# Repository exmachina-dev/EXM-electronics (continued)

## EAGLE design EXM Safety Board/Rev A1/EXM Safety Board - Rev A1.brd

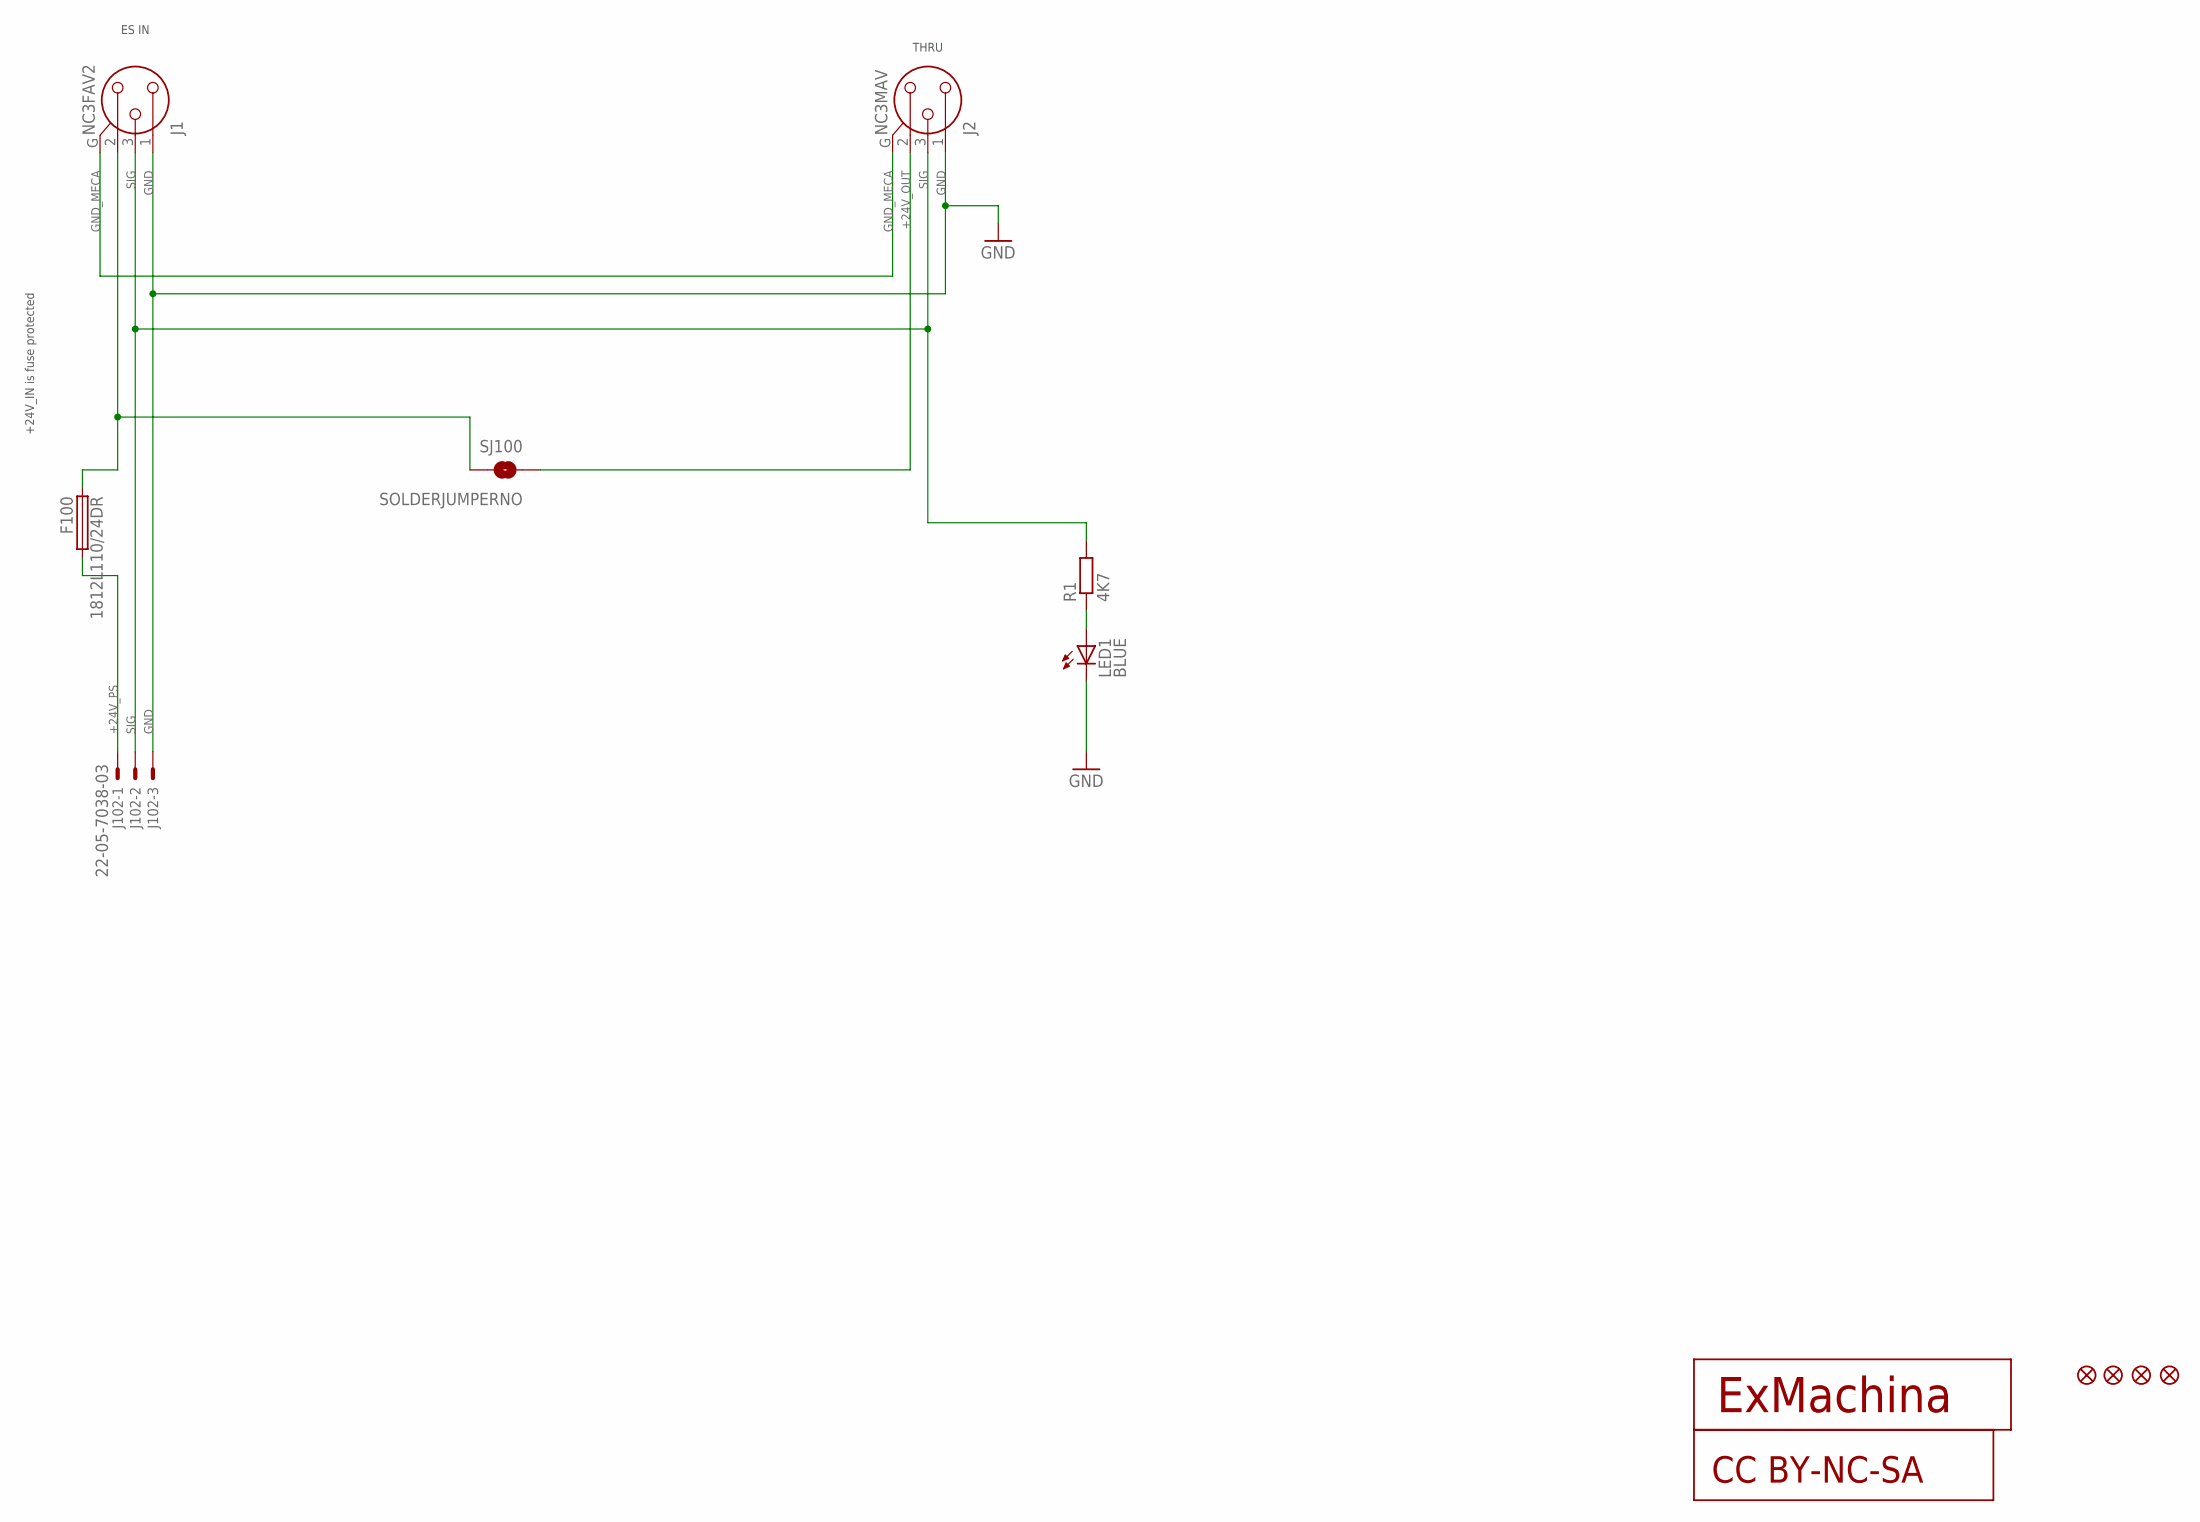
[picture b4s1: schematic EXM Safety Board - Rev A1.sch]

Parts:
CC100: CC-BY-NC-SA
F100: 1812L110/24DR; LITTLEFUSE_SMD; MPN 1812L110/24DR
J1: NC3FAV2
J2: NC3MAV
J102: 22-05-7038-03; 7395-03
JP100, JP101, JP102, JP103: FIDUCIAL1X2; FIDUCIAL-1X2
LED1: BLUE; CHIPLED_0603; MPN OVS-0603
R1: 4K7; R0603; MPN RC0603FR-074K7L
SJ100: SOLDERJUMPERNO; SJ_2S-NO
T100: EXMACHINA-LOGO-NAME; EXM-LOGO-BASELINE

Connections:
+24V_IN: F100.1, J1.2, SJ100.2
+24V_OUT: J2.2, SJ100.1
+24V_PS: F100.2, J102.1
GND: J1.1, J2.1, J102.3, LED1.C
GND_MECA: J1.G, J2.G
unnamed: LED1.A, R1.1
SIG: J1.3, J2.3, J102.2, R1.2

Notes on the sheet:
+24V_IN is fuse protected
ES IN
THRU

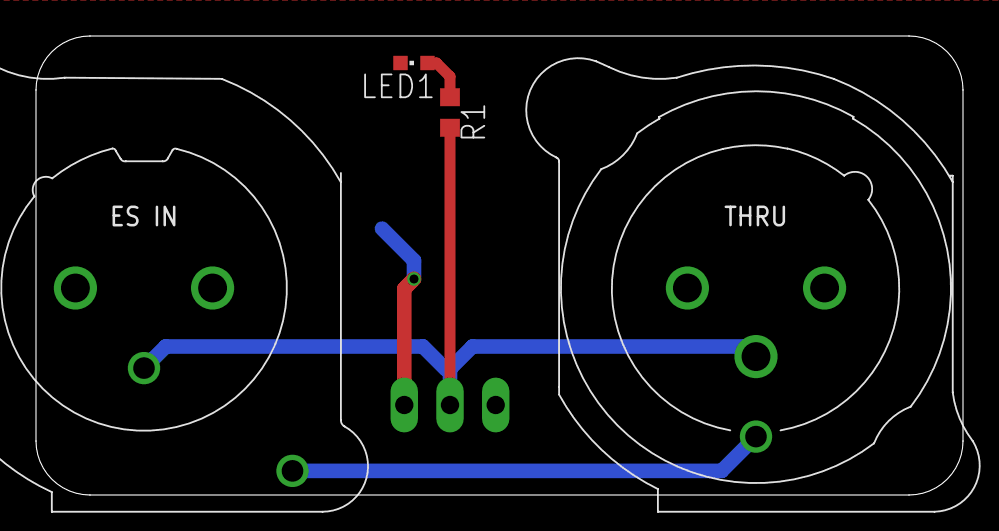
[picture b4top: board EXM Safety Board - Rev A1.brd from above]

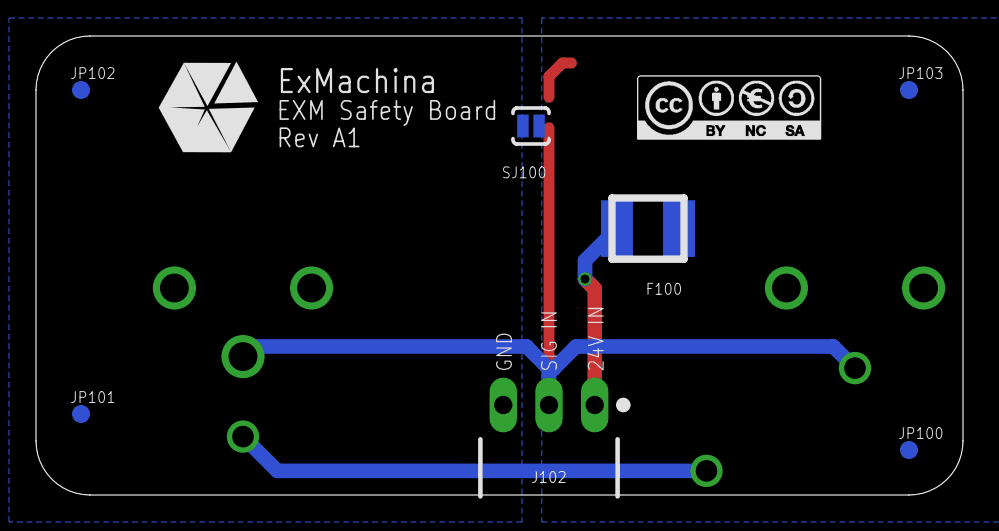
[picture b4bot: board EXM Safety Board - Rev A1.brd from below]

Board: 2 copper layers, 51.5 x 25.5 mm, 14 parts (9 on the bottom side), 7 nets.

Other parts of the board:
U$1: A4L-LOC

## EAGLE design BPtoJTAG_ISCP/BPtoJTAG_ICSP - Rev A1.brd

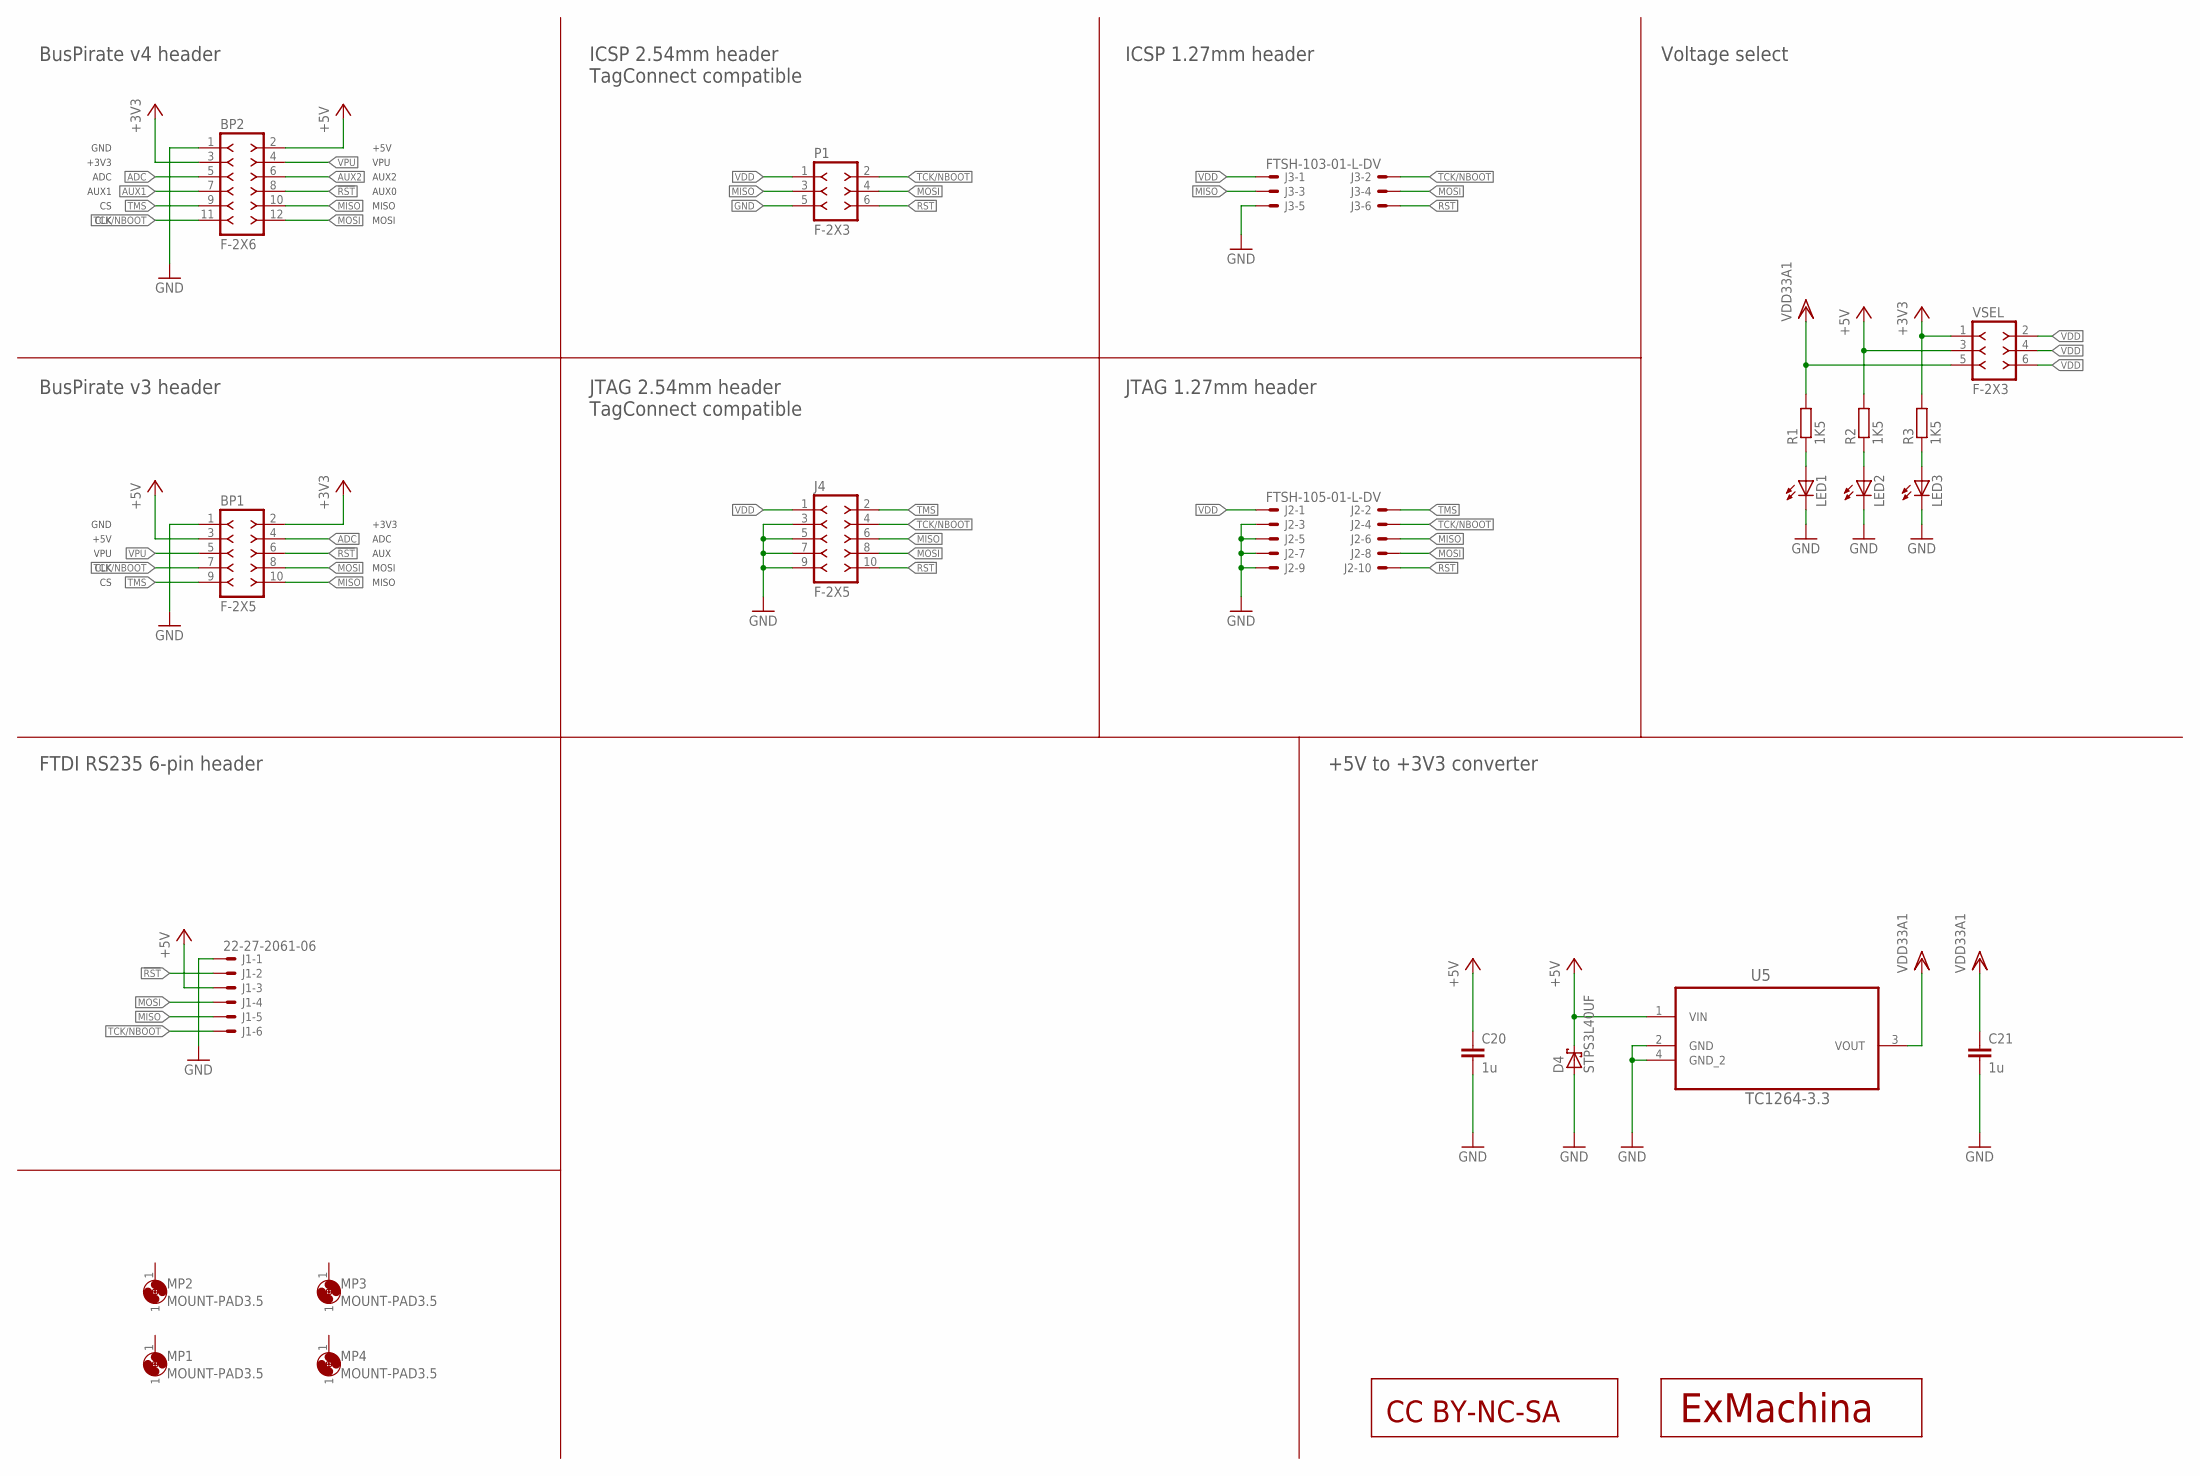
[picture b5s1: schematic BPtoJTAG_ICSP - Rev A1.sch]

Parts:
BP1: F-2X5; DIL-100-2X5
BP2: F-2X6; DIL-100-2X6
C20, C21: 1u; C0603
CC1: CC-BY-NC-SA
D4: STPS3L40UF; SMB
J1: 22-27-2061-06; 6410-06
J2: FTSH-105-01-L-DV
J3: FTSH-103-01-L-DV
J4: F-2X5; DIL-100-2X5
LED1, LED2, LED3: LEDCHIPLED_0603; CHIPLED_0603
MP1, MP2, MP3, MP4: MOUNT-PAD3.5; P3,5
P1: F-2X3; DIL-100-2X3
R1, R2, R3: 1K5; R0603
T1: EXMACHINA-LOGO-NAME; EXM-LOGO-BASELINE
U5: TC1264-3.3; SOT230P700X180-4N
VSEL: F-2X3; DIL-100-2X3

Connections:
!RST: BP1.6, BP2.8, J1.2, J2.10, J3.6, J4.10, P1.6
+3V3: BP1.2, BP2.3, R3.2, VSEL.1
+5V: BP1.3, BP2.2, C20.1, D4.C, J1.3, R2.2, U5.1 (VIN), VSEL.3
ADC: BP1.4, BP2.5
AUX1: BP2.7
AUX2: BP2.6
GND: BP1.1, BP2.1, C20.2, C21.2, D4.A, J1.1, J2.3, J2.5, J2.7, J2.9, J3.5, J4.3, J4.5, J4.7, J4.9, LED1.C, LED2.C, LED3.C, P1.5, U5.2 (GND), U5.4 (GND_2)
MISO: BP1.10, BP2.10, J1.5, J2.6, J3.3, J4.6, P1.3
MOSI: BP1.8, BP2.12, J1.4, J2.8, J3.4, J4.8, P1.4
unnamed: LED1.A, R1.1
unnamed: LED2.A, R2.1
unnamed: LED3.A, R3.1
TCK/NBOOT: BP1.7, BP2.11, J1.6, J2.4, J3.2, J4.4, P1.2
TMS: BP1.9, BP2.9, J2.2, J4.2
VDD: J2.1, J3.1, J4.1, P1.1, VSEL.2, VSEL.4, VSEL.6
VDD33A1: C21.1, R1.2, U5.3 (VOUT), VSEL.5
VPU: BP1.5, BP2.4

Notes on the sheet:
GND
+5V
VPU
CLK
+3V3
ADC
AUX
MOSI
MISO
AUX0
AUX2
AUX1
BusPirate v4 header
BusPirate v3 header
Voltage select
FTDI RS235 6-pin header
JTAG 1.27mm header
JTAG 2.54mm header TagConnect compatible
ICSP 2.54mm header TagConnect compatible
ICSP 1.27mm header
+5V to +3V3 converter

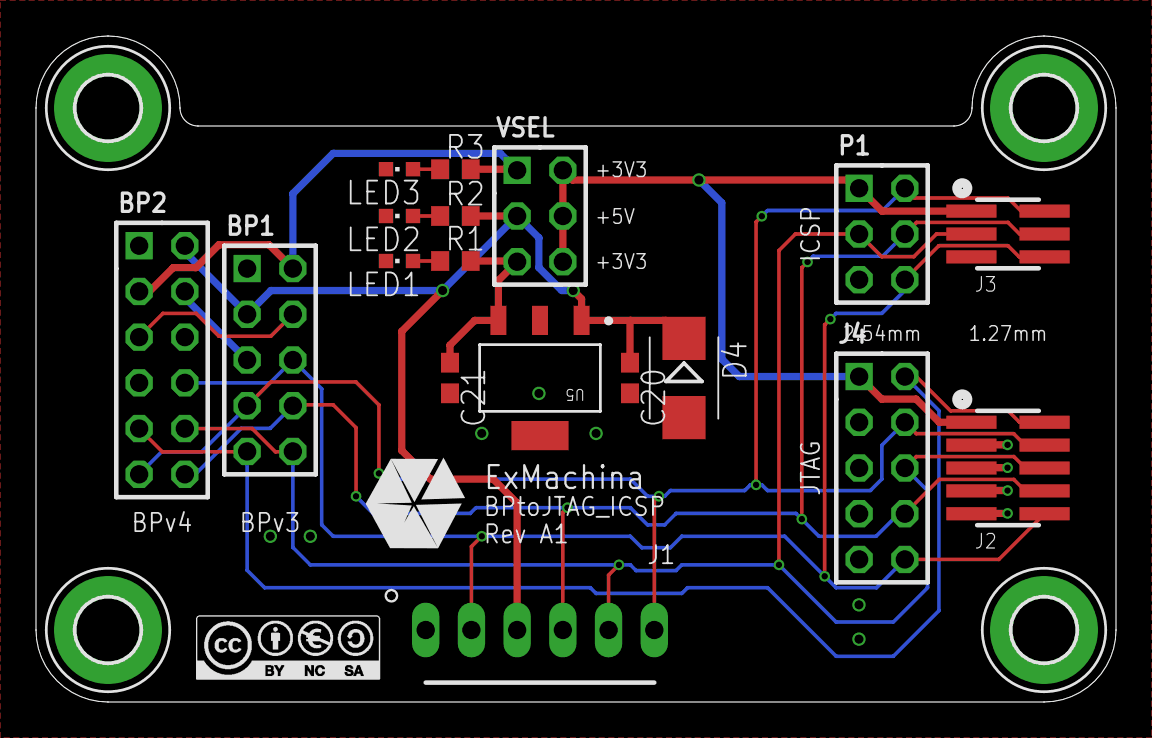
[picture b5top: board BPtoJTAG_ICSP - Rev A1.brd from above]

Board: 2 copper layers, 60.0 x 37.0 mm, 24 parts (0 on the bottom side), 15 nets.

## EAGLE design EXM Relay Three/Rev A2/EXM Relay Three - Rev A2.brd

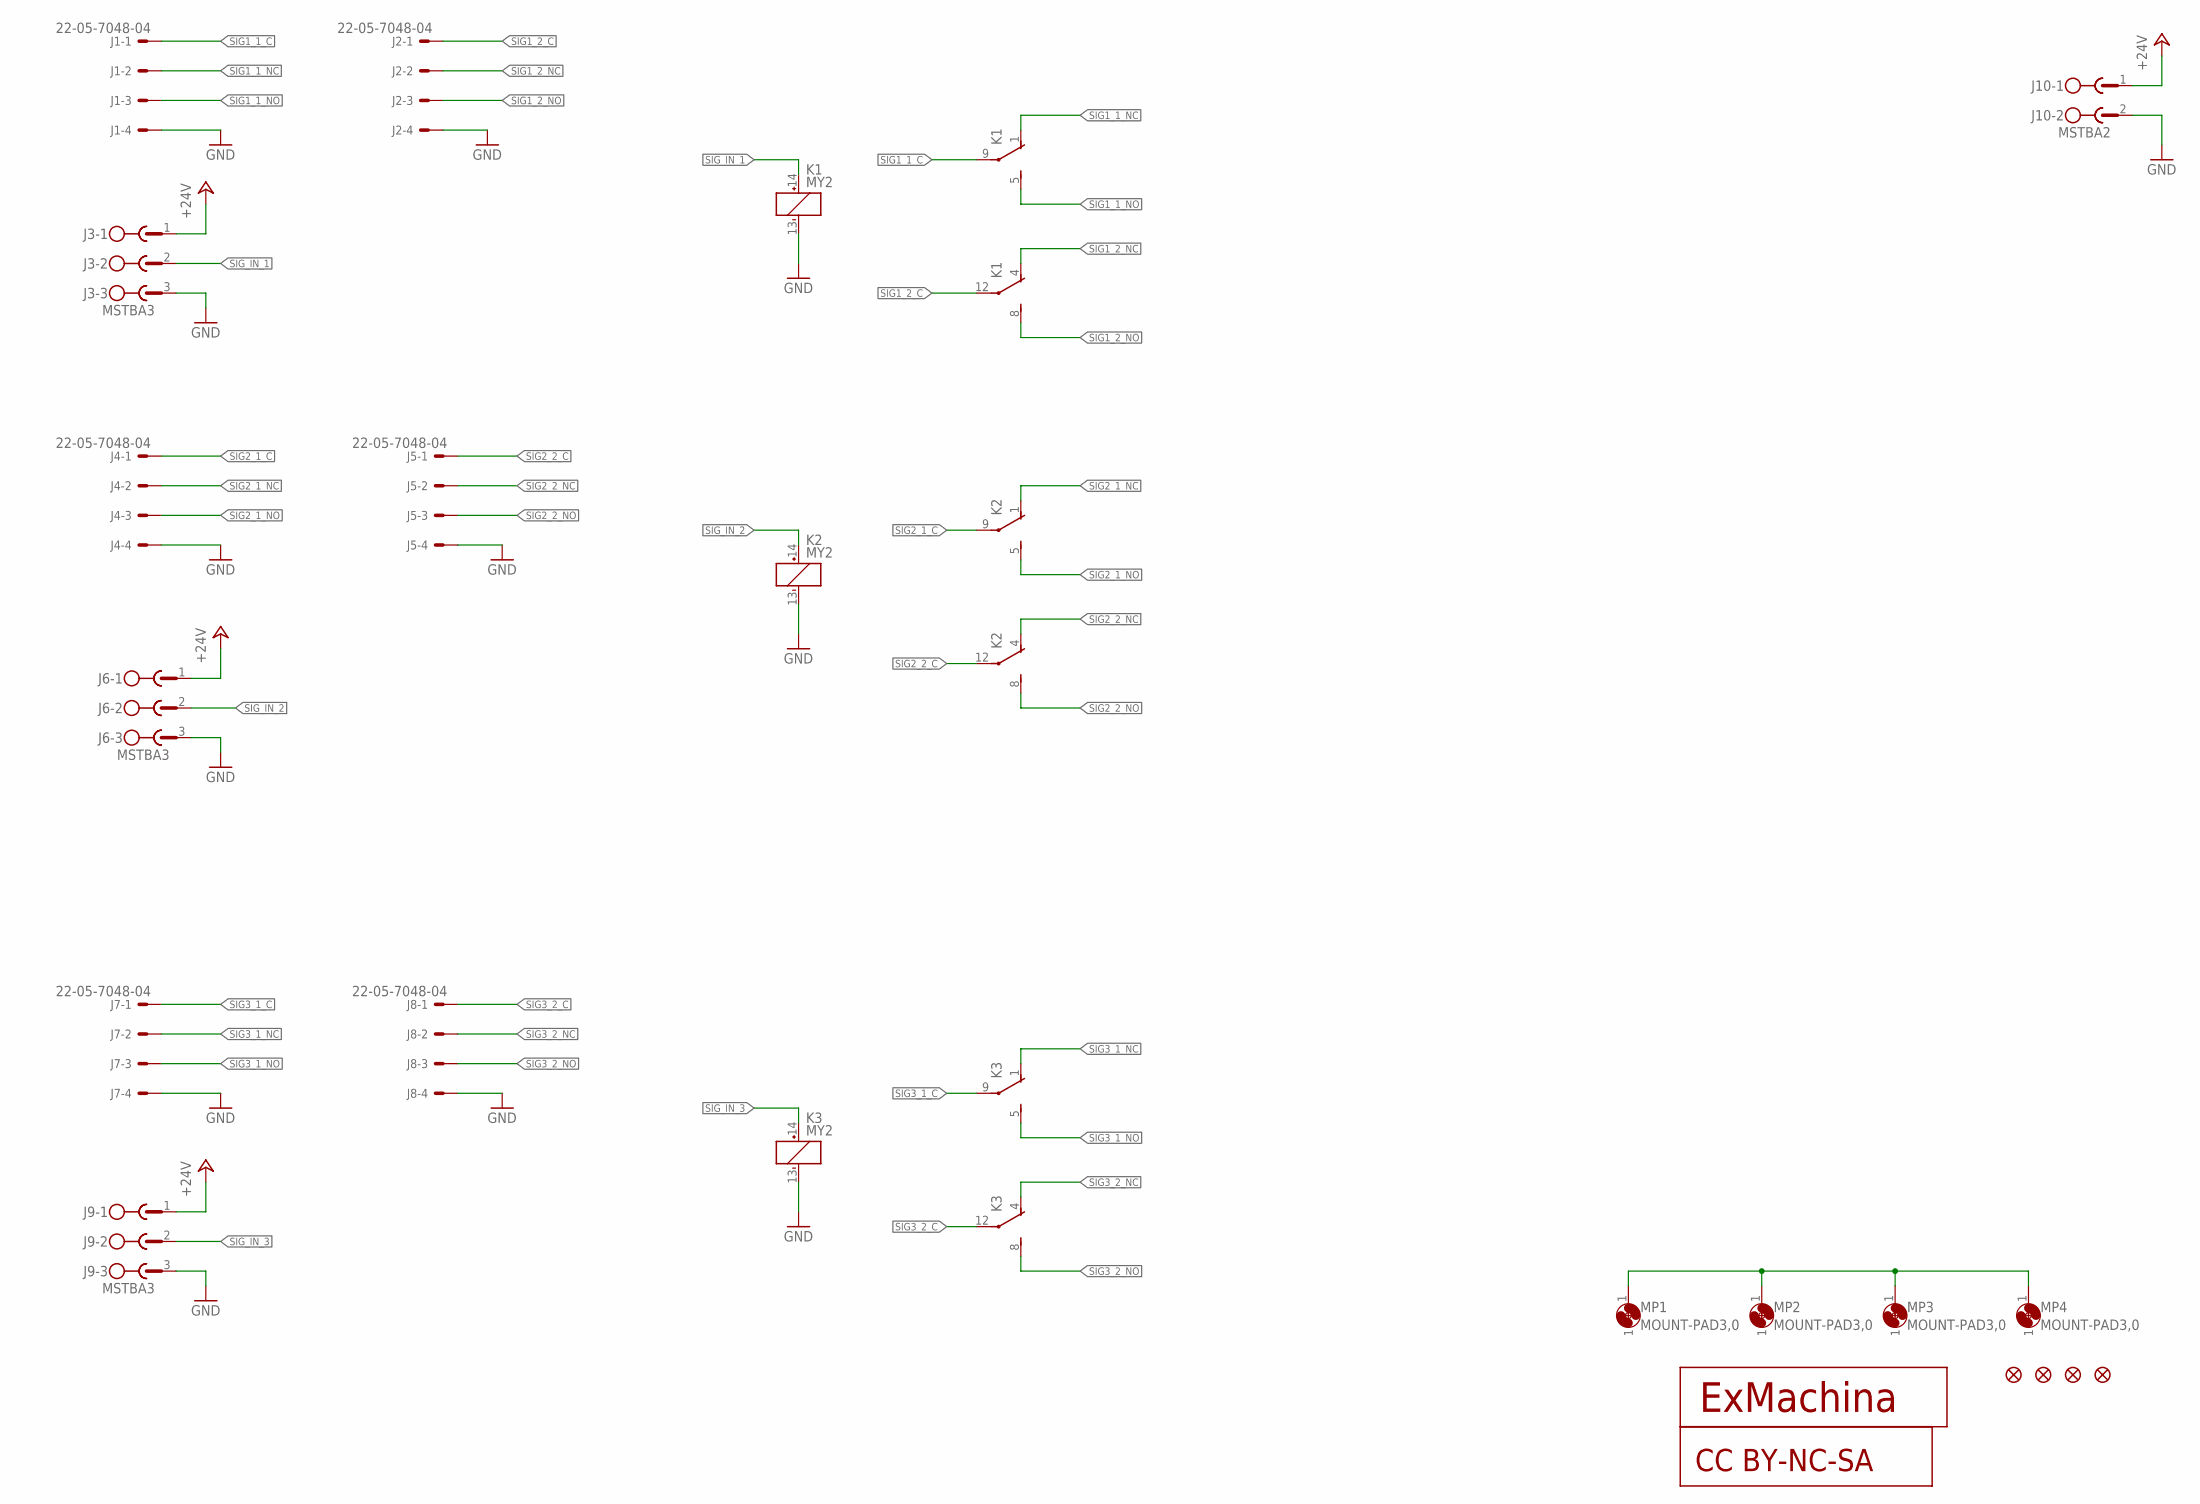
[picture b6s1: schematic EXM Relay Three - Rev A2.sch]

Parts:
CC1: CC-BY-NC-SA
J1, J2, J4, J5, J7, J8: 22-05-7048-04; 7395-04
J3, J6, J9: MSTBA3
J10: MSTBA2
JP1, JP2, JP3, JP4: FIDUCIAL1X2; FIDUCIAL-1X2
K1, K2, K3: MY2; PY08; MPN PY08
MP1, MP2, MP3, MP4: MOUNT-PAD3,0; P3,0
T1: EXMACHINA-LOGO-NAME; EXM-LOGO-BASELINE

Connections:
1: MP1.1, MP2.1, MP3.1, MP4.1
+24V: J3.1, J6.1, J9.1, J10.1
GND: J1.4, J2.4, J3.3, J4.4, J5.4, J6.3, J7.4, J8.4, J9.3, J10.2, K1.13 (-), K2.13 (-), K3.13 (-)
SIG1_1_C: J1.1, K1.9 (C)
SIG1_1_NC: J1.2, K1.1 (NC)
SIG1_1_NO: J1.3, K1.5 (NO)
SIG1_2_C: J2.1, K1.12 (C)
SIG1_2_NC: J2.2, K1.4 (NC)
SIG1_2_NO: J2.3, K1.8 (NO)
SIG2_1_C: J4.1, K2.9 (C)
SIG2_1_NC: J4.2, K2.1 (NC)
SIG2_1_NO: J4.3, K2.5 (NO)
SIG2_2_C: J5.1, K2.12 (C)
SIG2_2_NC: J5.2, K2.4 (NC)
SIG2_2_NO: J5.3, K2.8 (NO)
SIG3_1_C: J7.1, K3.9 (C)
SIG3_1_NC: J7.2, K3.1 (NC)
SIG3_1_NO: J7.3, K3.5 (NO)
SIG3_2_C: J8.1, K3.12 (C)
SIG3_2_NC: J8.2, K3.4 (NC)
SIG3_2_NO: J8.3, K3.8 (NO)
SIG_IN_1: J3.2, K1.14 (+)
SIG_IN_2: J6.2, K2.14 (+)
SIG_IN_3: J9.2, K3.14 (+)

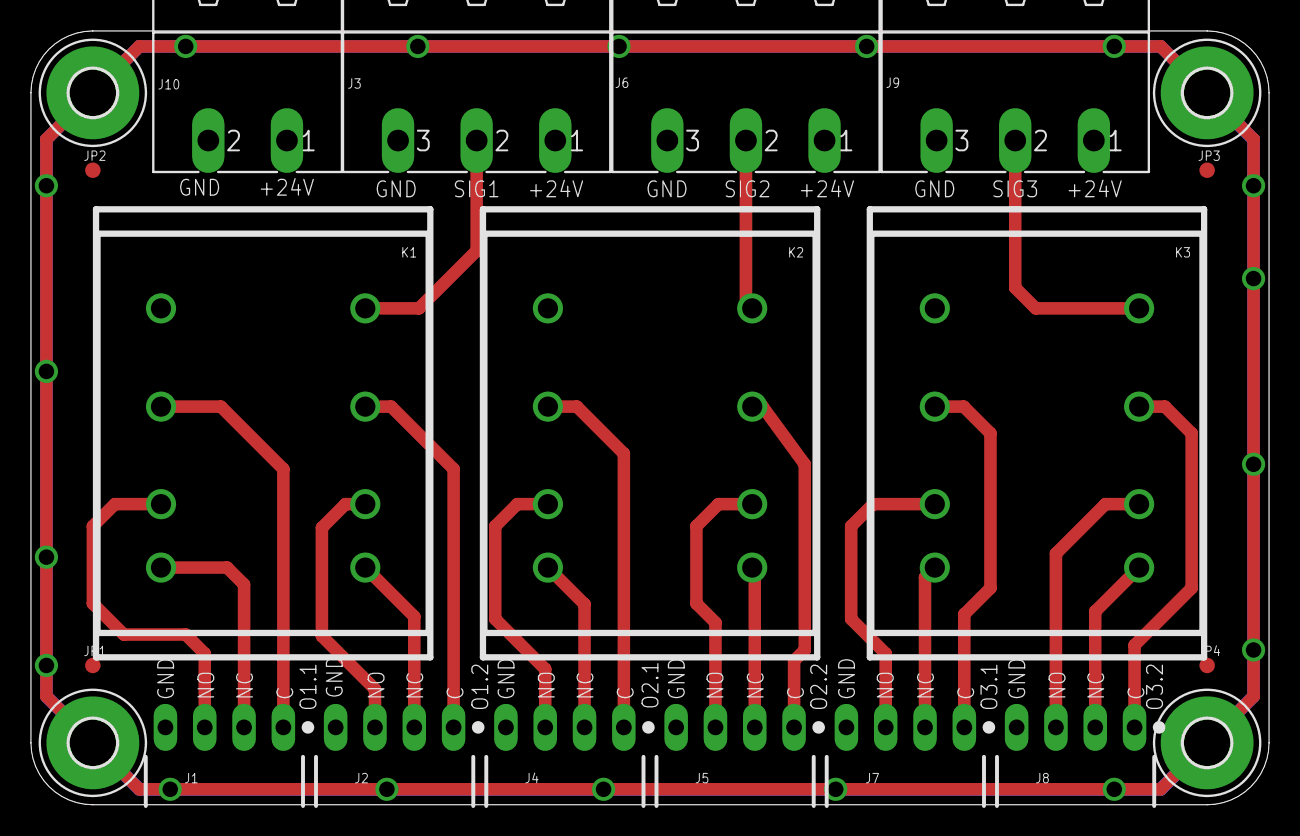
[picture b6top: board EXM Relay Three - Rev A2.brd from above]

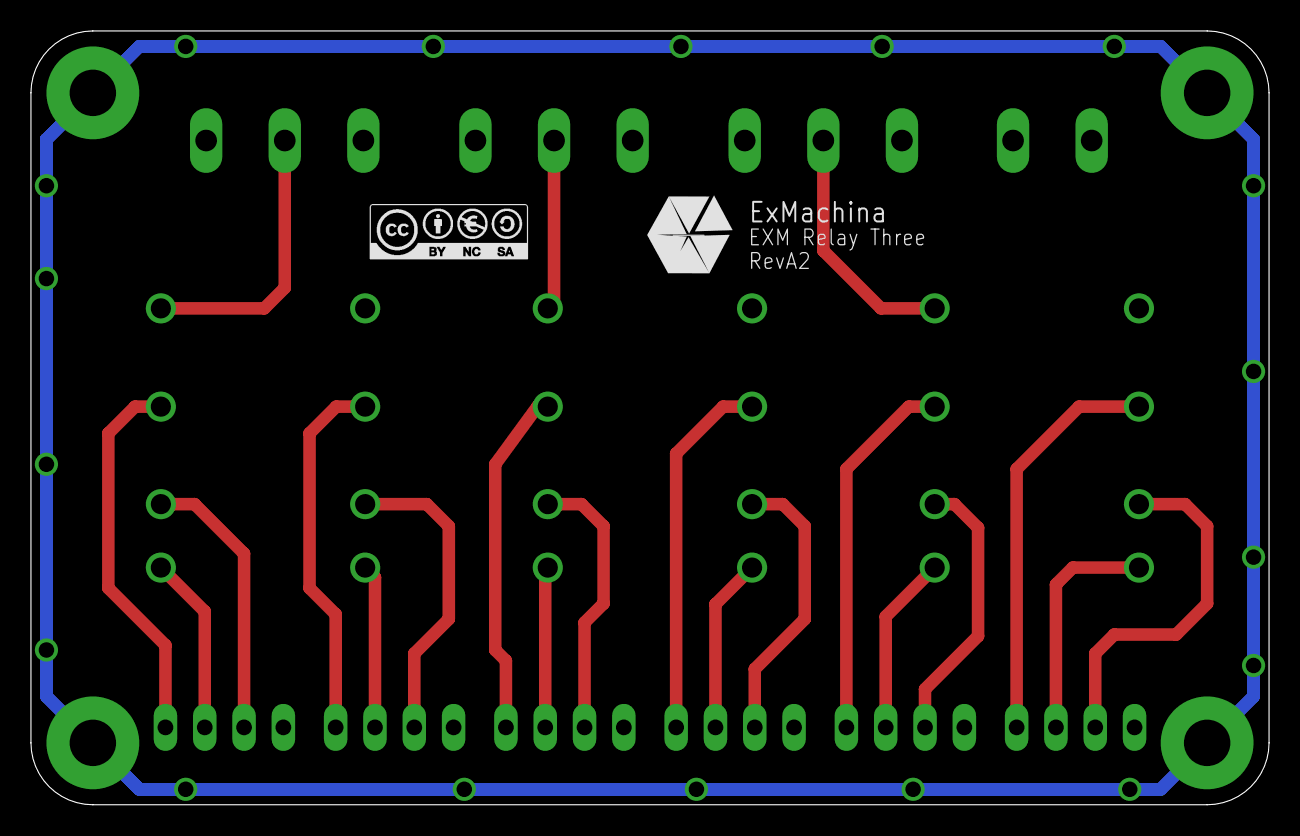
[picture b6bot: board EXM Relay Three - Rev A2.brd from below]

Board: 2 copper layers, 80.0 x 50.0 mm, 24 parts (2 on the bottom side), 24 nets.

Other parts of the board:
U$1: A4L-LOC

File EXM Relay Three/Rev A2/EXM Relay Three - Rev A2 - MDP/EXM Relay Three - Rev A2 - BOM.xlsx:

Qty | Designator | Value | Description | Package | Manufacteur | Reference Manufacteur | Mounting Tecghnologie | Mount
6 | J1, J2, J4, J5, J7, J8 | 22-05-7048 | Connecteur fil-à-carte, Angle Droit, 2.54 mm, 4 Contact(s), Embase, Série KK |  | MOLEX | 22-05-7048 | Thought-Hole | Yes
1 | J10 | MSTBA2 | Bornier, Embase, 5.08 mm, 2 Voies, 12 A, 250 V, Traversant angle droit |  | PHOENIX | 1757242 | Thought-Hole | Yes
3 | J3, J6, J9 | MSTBA3 | Bornier, Embase, 5.08 mm, 3 Voies, 12 A, 250 V, Traversant angle droit |  | PHOENIX | 1757255 | Thought-Hole | Yes
3 | K1, K2, K3 | PY08-02 | Embase relais, Traversant, Connexion rapide, 8 Broche(s), 7 A, 250 VAC, SUPER M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 |  | OMRON COMPONENTS USA | PY08-02 | Thought-Hole | Yes
3 |  | PYC-P2 | Accessoire pour relais, MY/LY Series, Maintien bas |  | OMRON COMPONENTS USA | PYC-P2

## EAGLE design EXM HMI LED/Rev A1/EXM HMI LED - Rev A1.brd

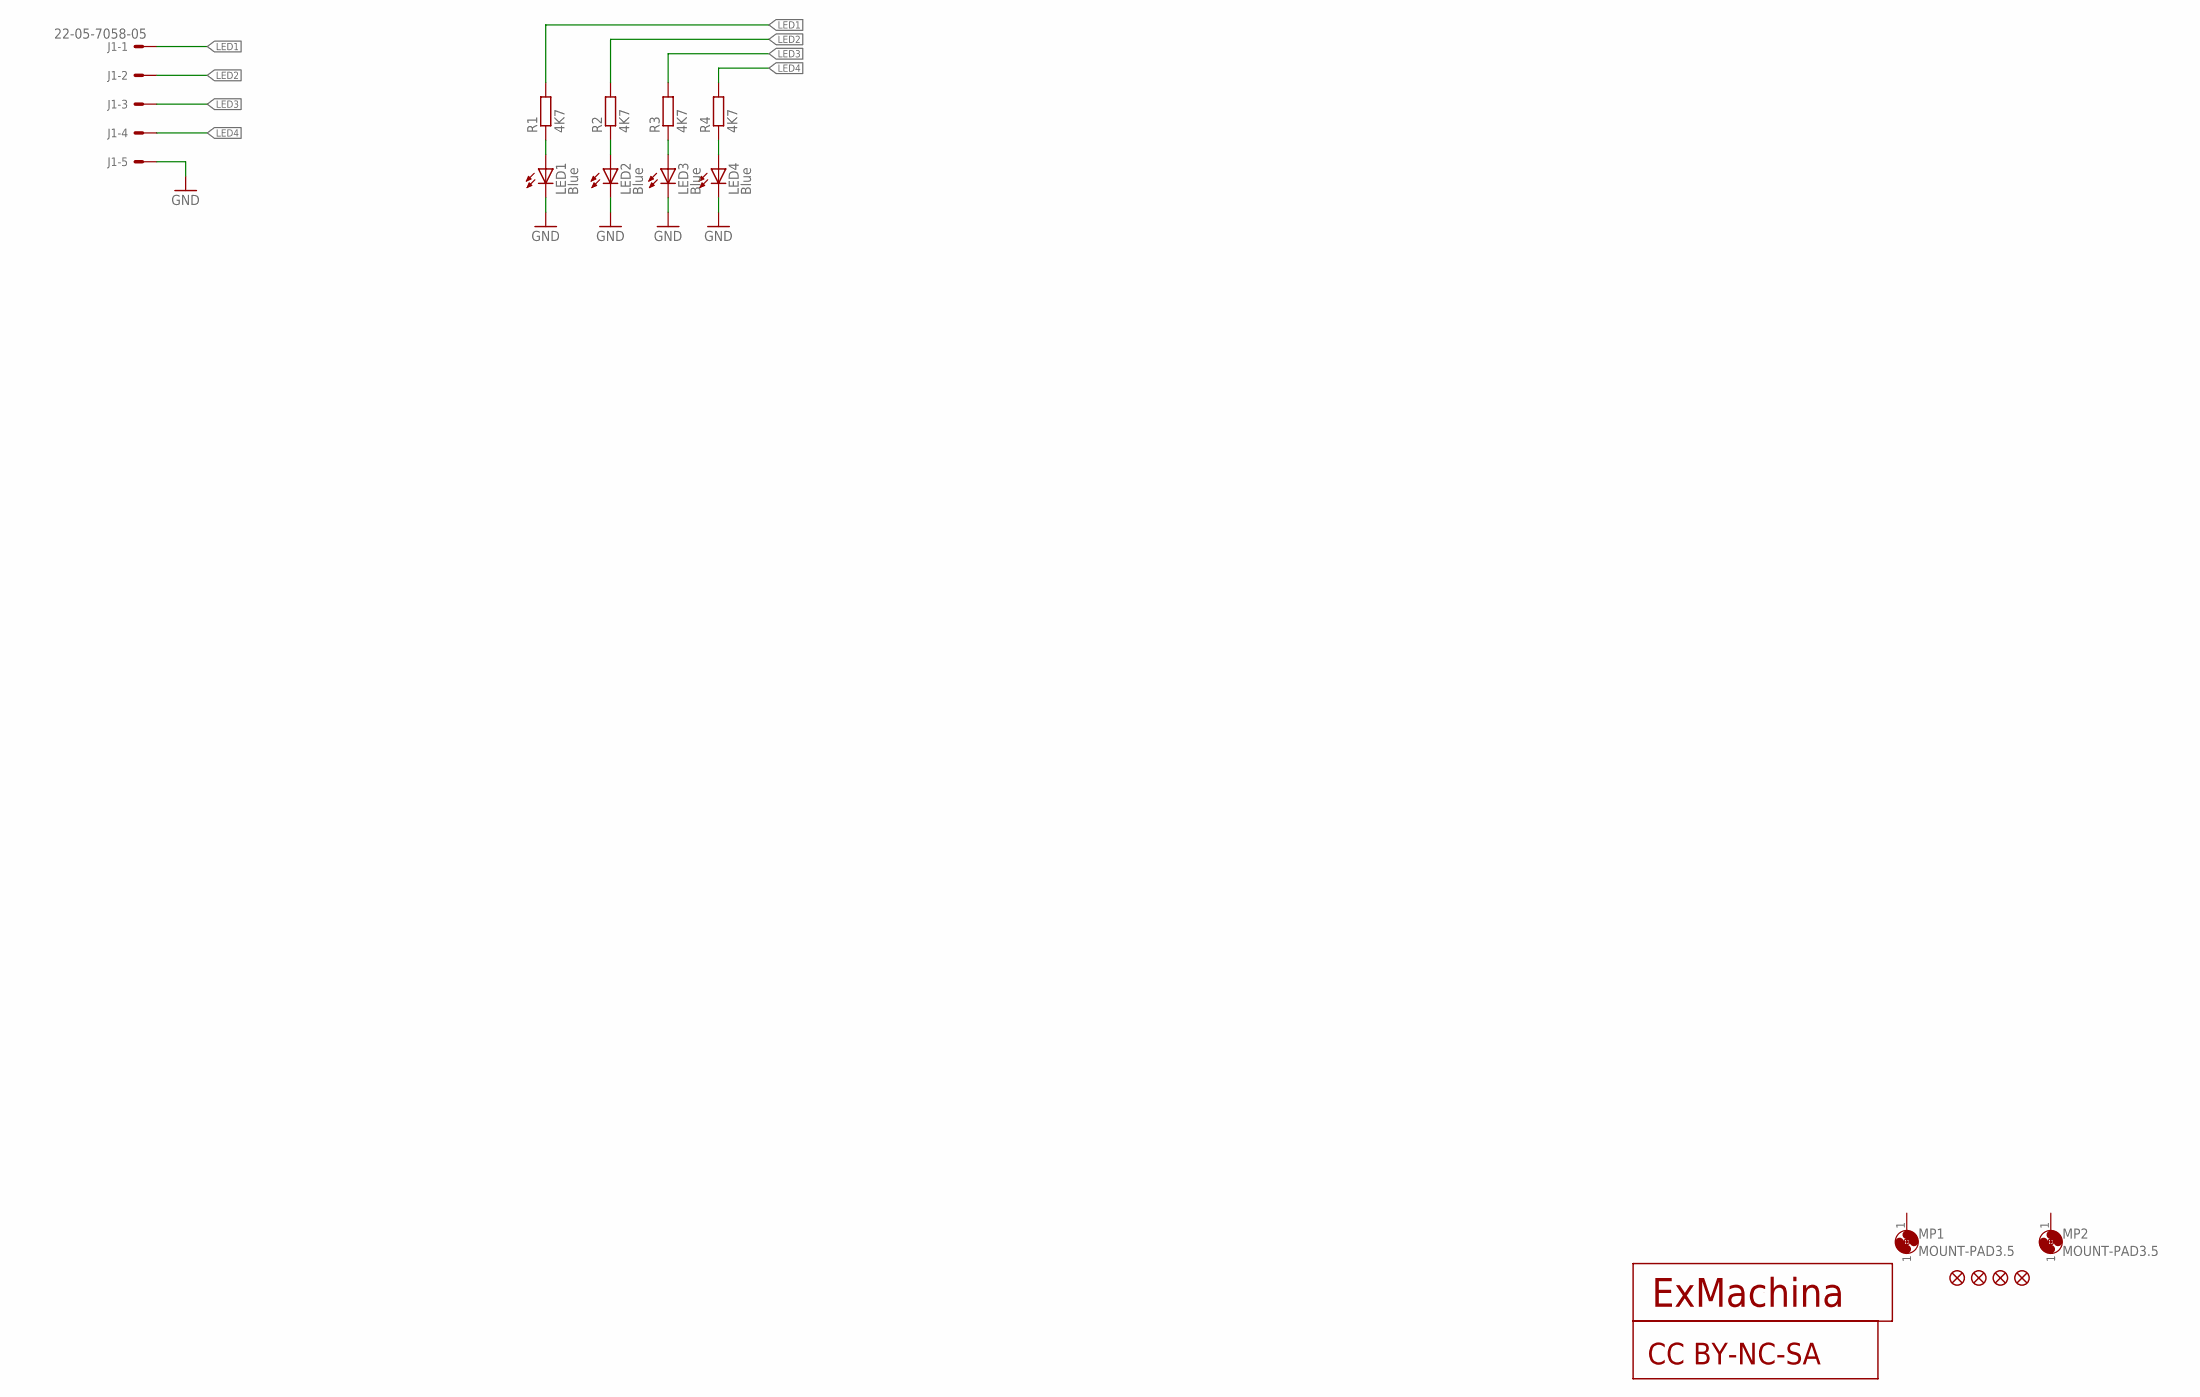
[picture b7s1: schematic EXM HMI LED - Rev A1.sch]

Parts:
CC1: CC-BY-NC-SA
J1: 22-05-7058-05; 7395-05
JP1, JP2, JP3, JP4: FIDUCIAL1X2; FIDUCIAL-1X2
LED1, LED2, LED3, LED4: Blue; CHIP-LED0603
MP1, MP2: MOUNT-PAD3.5; P3,5
R1, R2, R3, R4: 4K7; R0603
T1: EXMACHINA-LOGO-NAME; EXM-LOGO-BASELINE

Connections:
GND: J1.5, LED1.C, LED2.C, LED3.C, LED4.C
LED1: J1.1, R1.2
LED2: J1.2, R2.2
LED3: J1.3, R3.2
LED4: J1.4, R4.2
unnamed: LED4.A, R4.1
unnamed: LED3.A, R3.1
unnamed: LED2.A, R2.1
unnamed: LED1.A, R1.1

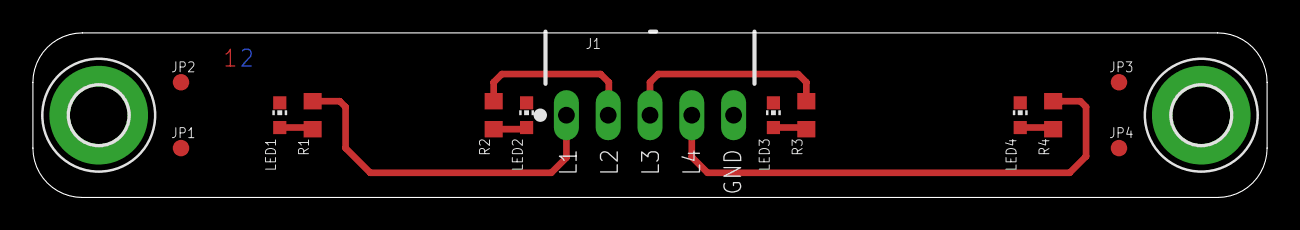
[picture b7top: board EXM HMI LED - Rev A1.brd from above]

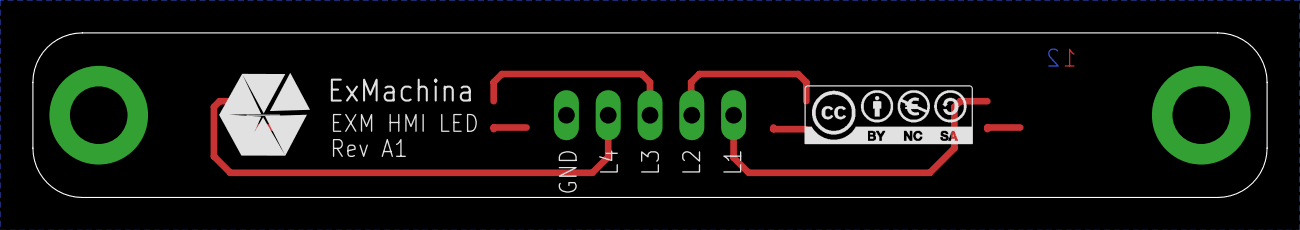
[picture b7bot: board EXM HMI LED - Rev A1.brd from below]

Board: 2 copper layers, 75.0 x 10.0 mm, 18 parts (2 on the bottom side), 9 nets.

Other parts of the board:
U$1: A4L-LOC
